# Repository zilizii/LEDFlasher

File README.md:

# LEDFlasher
KiCAD project for LED flasher based on CD4001

project as is an exact copy of : https://hackaday.io/project/28344-10-year-led-flasher

v0.2 exact copy of the link content
v0.3 improved design

Project Use for my Kids learn to solder and practice KiCAD 5.1.6 as hobbiest...

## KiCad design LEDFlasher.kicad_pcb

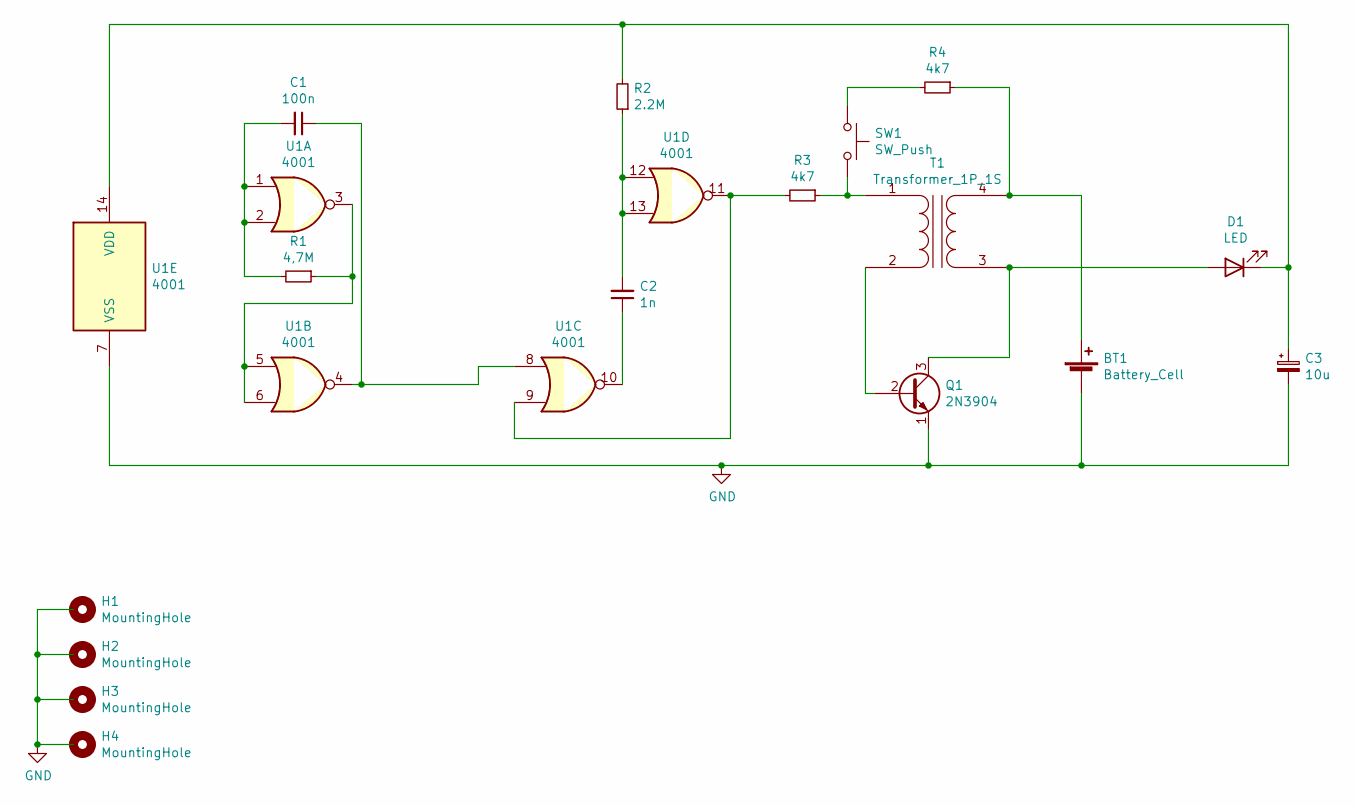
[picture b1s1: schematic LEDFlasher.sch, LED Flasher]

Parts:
BT1: Battery_Cell; BatteryHolder_Keystone_2460_1xAA
C1: 100n; C_Disc_D6.0mm_W4.4mm_P5.00mm
C2: 1n; C_Disc_D6.0mm_W4.4mm_P5.00mm
C3: 10u; CP_Radial_D5.0mm_P2.50mm
D1: LED; LED_D5.0mm
H1, H2, H3, H4: MountingHole; MountingHole_2.5mm_Pad
Q1: 2N3904; TO-92_Inline
R1: 4,7M; R_Axial_DIN0204_L3.6mm_D1.6mm_P7.62mm_Horizontal
R2: 2.2M; R_Axial_DIN0204_L3.6mm_D1.6mm_P7.62mm_Horizontal
R3, R4: 4k7; R_Axial_DIN0204_L3.6mm_D1.6mm_P7.62mm_Horizontal
SW1: SW_Push; SW_SPST_CK_RS282G05A3
T1: Transformer_1P_1S; Transformer_Toroid_Horizontal_D9.0mm_Amidon-T30
U1: 4001; DIP-14_W7.62mm_LongPads

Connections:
GND: BT1.2 (-), C3.2, Q1.1 (E), U1.7 (VSS)
unnamed: BT1.1 (+), R4.1, T1.4 (SB)
unnamed: C1.1, U1.4, U1.8
unnamed: C1.2, R1.2, U1.1, U1.2
unnamed: C2.1, U1.10
unnamed: C2.2, R2.1, U1.12, U1.13
unnamed: C3.1, D1.1 (K), R2.2, U1.14 (VDD)
unnamed: D1.2 (A), Q1.3 (C), T1.3 (SA)
unnamed: Q1.2 (B), T1.2 (AB)
unnamed: R1.1, U1.3, U1.5, U1.6
unnamed: R3.1, SW1.2, T1.1 (AA)
unnamed: R3.2, U1.9, U1.11
unnamed: R4.2, SW1.1

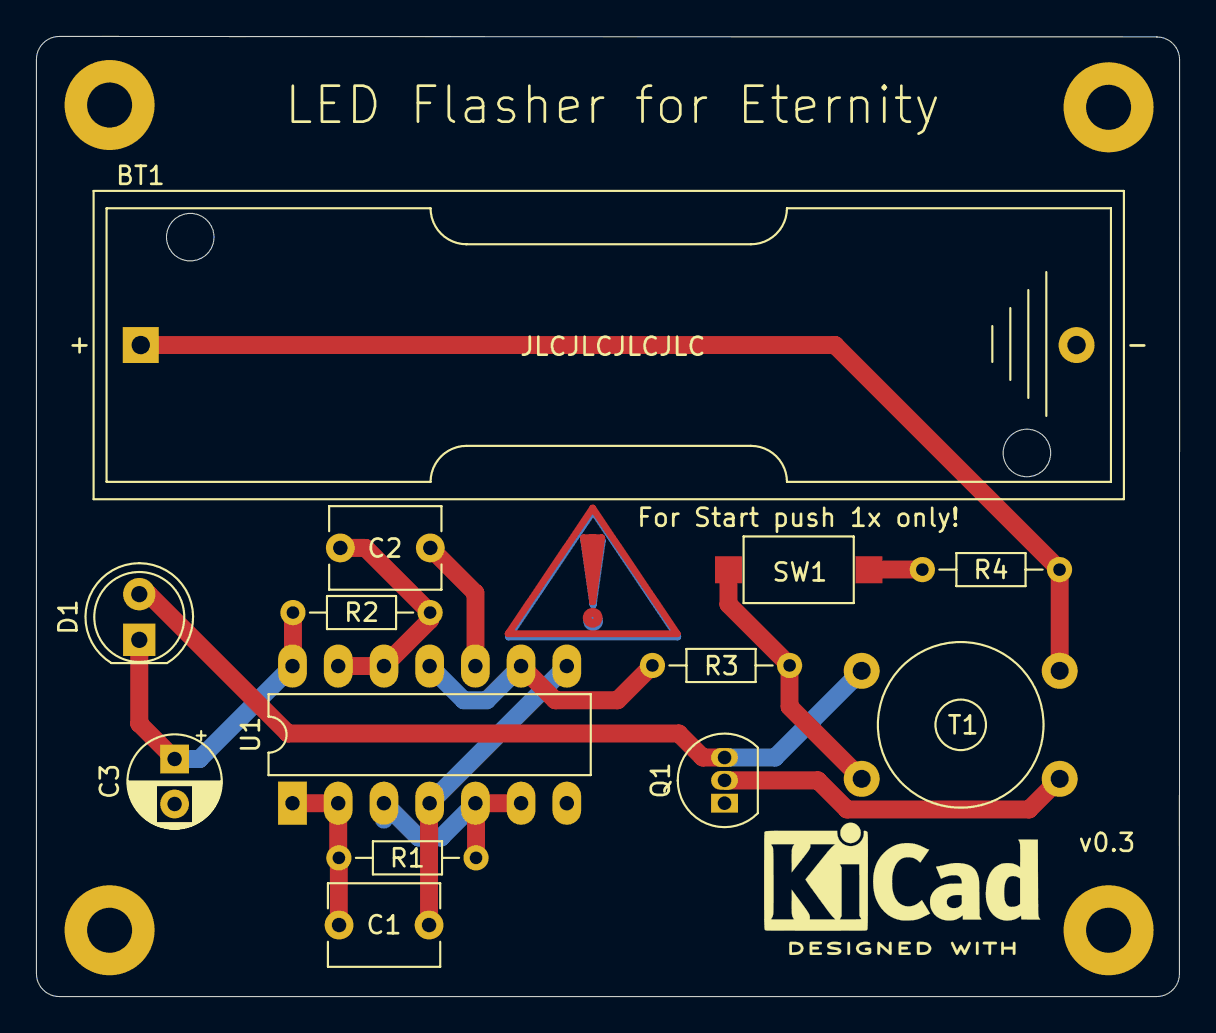
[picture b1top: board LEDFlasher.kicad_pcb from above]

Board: 2 copper layers, 63.5 x 53.3 mm, 17 parts (0 on the bottom side), 13 nets.

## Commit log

2021-01-21 v0.2
2021-01-22 Review changes
2021-01-22 Readme updated
2021-01-22 Gerber for v0.3
2021-01-25 v0.3 production
2021-01-25 Create LICENSE
